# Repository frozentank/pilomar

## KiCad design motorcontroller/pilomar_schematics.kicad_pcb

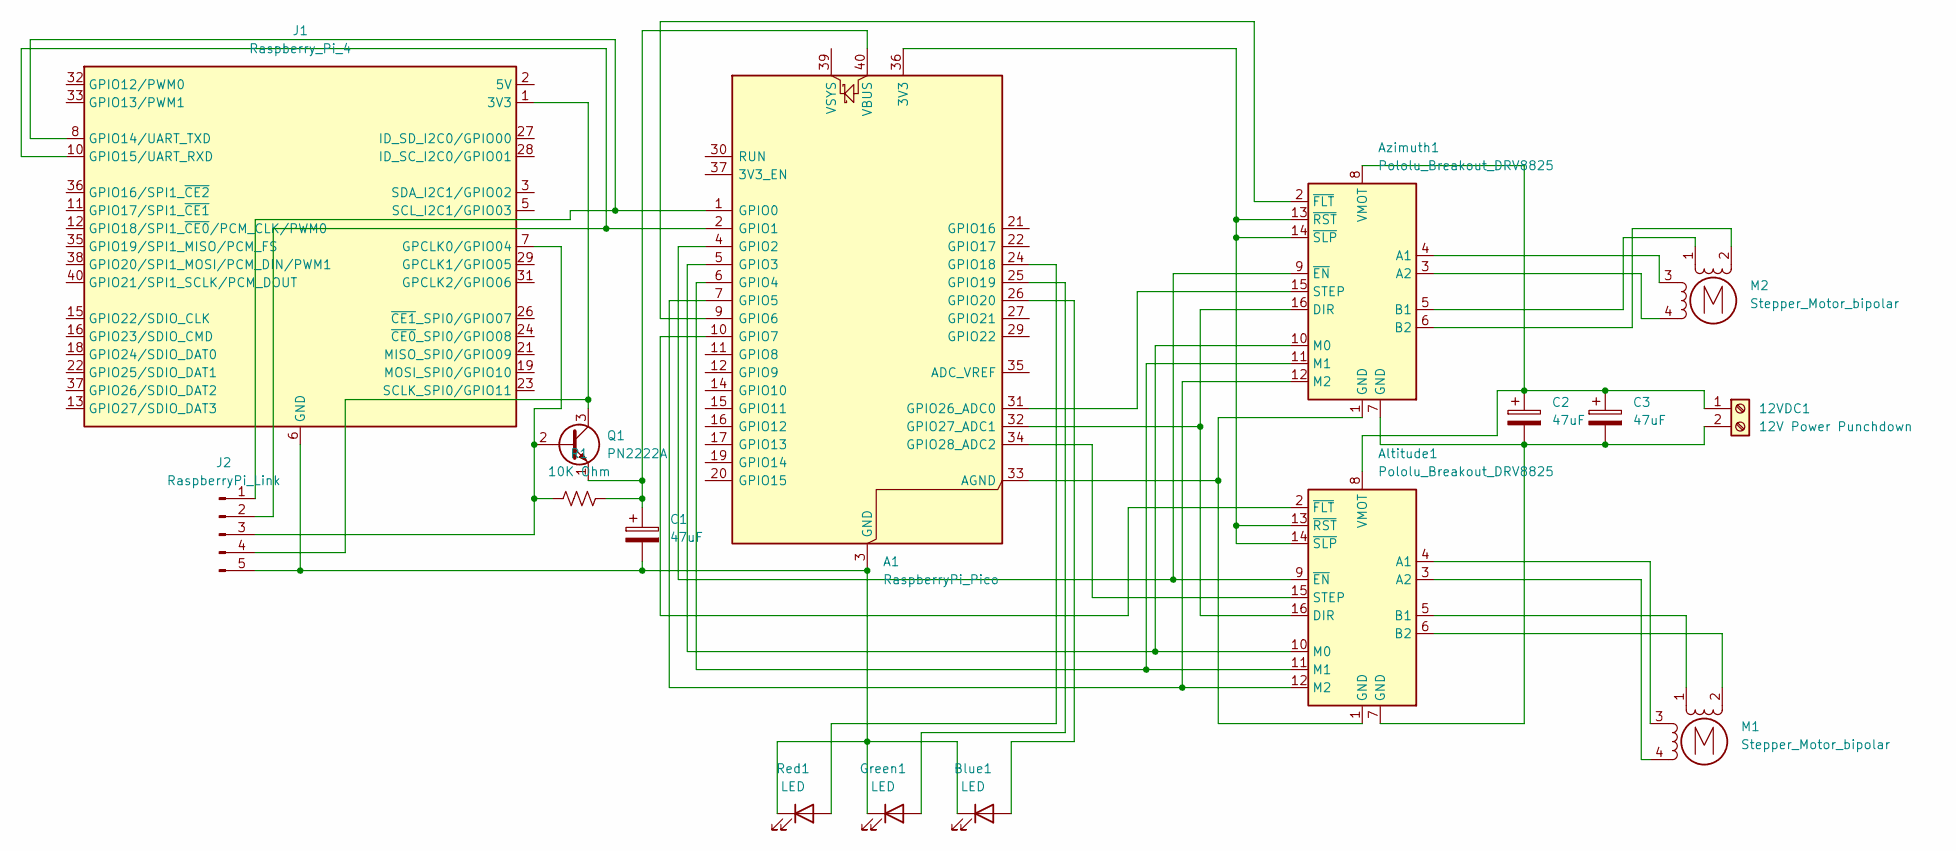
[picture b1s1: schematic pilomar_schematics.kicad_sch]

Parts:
12VDC1: 12V Power Punchdown; TerminalBlock_bornier-2_P5.08mm
A1: RaspberryPi_Pico; RaspberryPi_Pico_Common_THT
Altitude1: Pololu_Breakout_DRV8825; Pololu_Breakout-16_15.2x20.3mm
Azimuth1: Pololu_Breakout_DRV8825; Pololu_Breakout-16_15.2x20.3mm
Blue1: LED; LED_D5.0mm
C1, C2, C3: 47uF; CP_Radial_D4.0mm_P1.50mm
Green1: LED; LED_D5.0mm
J1: Raspberry_Pi_4; PinHeader_2x20_P2.54mm_Vertical
J2: RaspberryPi_Link; PinHeader_1x05_P2.54mm_Vertical
M1, M2: Stepper_Motor_bipolar; PinHeader_1x04_P2.54mm_Vertical
Q1: PN2222A; TO-92_Inline
R1: 10K Ohm; R_Axial_DIN0204_L3.6mm_D1.6mm_P7.62mm_Horizontal
Red1: LED; LED_D5.0mm

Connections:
unnamed: 12VDC1.1, Altitude1.8 (VMOT), Azimuth1.8 (VMOT), C2.1, C3.1
unnamed: 12VDC1.2, Altitude1.7 (GND), Azimuth1.7 (GND), C2.2, C3.2
unnamed: A1.36 (3V3), Altitude1.13 (~RST), Altitude1.14 (~SLP), Azimuth1.13 (~RST), Azimuth1.14 (~SLP)
unnamed: A1.33 (AGND), Altitude1.1 (GND), Azimuth1.1 (GND)
unnamed: A1.1 (GPIO0), J1.8 (GPIO14/UART_TXD), J2.1
unnamed: A1.2 (GPIO1), J1.10 (GPIO15/UART_RXD), J2.2
unnamed: A1.4 (GPIO2), Altitude1.9 (~EN), Azimuth1.9 (~EN)
unnamed: A1.5 (GPIO3), Altitude1.10 (M0), Azimuth1.10 (M0)
unnamed: A1.6 (GPIO4), Altitude1.11 (M1), Azimuth1.11 (M1)
unnamed: A1.7 (GPIO5), Altitude1.12 (M2), Azimuth1.12 (M2)
unnamed: A1.9 (GPIO6), Azimuth1.2 (~FLT)
unnamed: A1.10 (GPIO7), Altitude1.2 (~FLT)
unnamed: A1.24 (GPIO18), Red1.2 (A)
unnamed: A1.25 (GPIO19), Green1.2 (A)
unnamed: A1.26 (GPIO20), Blue1.2 (A)
unnamed: A1.31 (GPIO26_ADC0), Azimuth1.15 (STEP)
unnamed: A1.32 (GPIO27_ADC1), Altitude1.16 (DIR), Azimuth1.16 (DIR)
unnamed: A1.34 (GPIO28_ADC2), Altitude1.15 (STEP)
unnamed: A1.40 (VBUS), C1.1, Q1.1 (E), R1.2
unnamed: Altitude1.4 (A1), M1.3
unnamed: Altitude1.3 (A2), M1.4
unnamed: Altitude1.5 (B1), M1.1
unnamed: Altitude1.6 (B2), M1.2 (-)
unnamed: Azimuth1.4 (A1), M2.3
unnamed: Azimuth1.3 (A2), M2.4
unnamed: Azimuth1.5 (B1), M2.1
unnamed: Azimuth1.6 (B2), M2.2 (-)
unnamed: A1.3 (GND), A1.8 (GND), A1.13 (GND), A1.18 (GND), A1.23 (GND), A1.28 (GND), A1.38 (GND), Blue1.1 (K), C1.2, Green1.1 (K), J1.6 (GND), J1.9 (GND), J1.14 (GND), J1.20 (GND), J1.25 (GND), J1.30 (GND), J1.34 (GND), J1.39 (GND), J2.5, Red1.1 (K)
unnamed: J1.2 (5V), J1.4 (5V)
unnamed: J1.7 (GPCLK0/GPIO04), J2.3, Q1.2 (B), R1.1
unnamed: J1.1 (3V3), J1.17 (3V3), J2.4, Q1.3 (C)

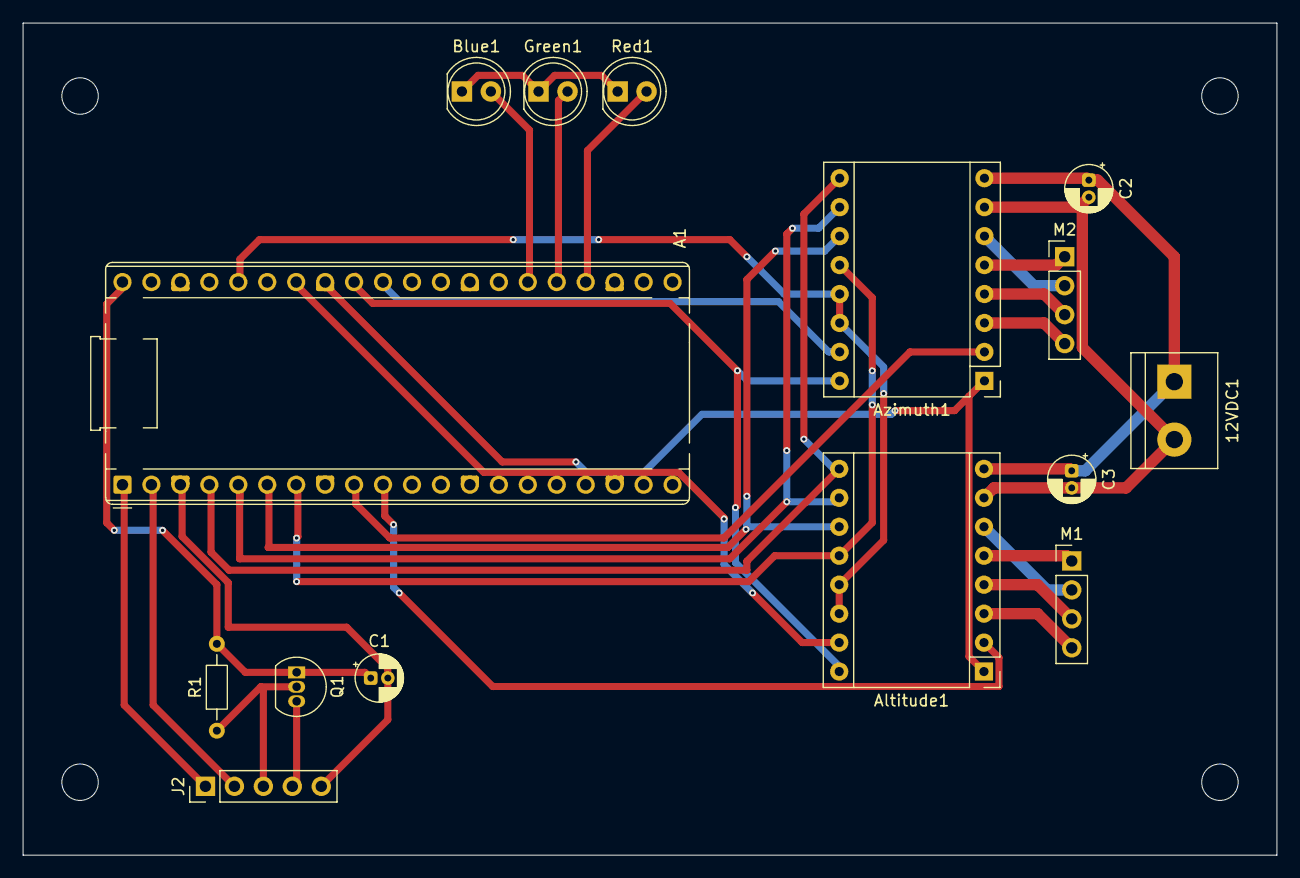
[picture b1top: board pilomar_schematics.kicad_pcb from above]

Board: 2 copper layers, 110.0 x 73.0 mm, 15 parts (0 on the bottom side), 30 nets.

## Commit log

2025-12-19 feat: Adding new motorcontroller board
